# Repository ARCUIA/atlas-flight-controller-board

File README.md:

# atlas-flight-controller-v3
Repository to track KiCad (v9.0) Project for our spr26 competition flight controller.

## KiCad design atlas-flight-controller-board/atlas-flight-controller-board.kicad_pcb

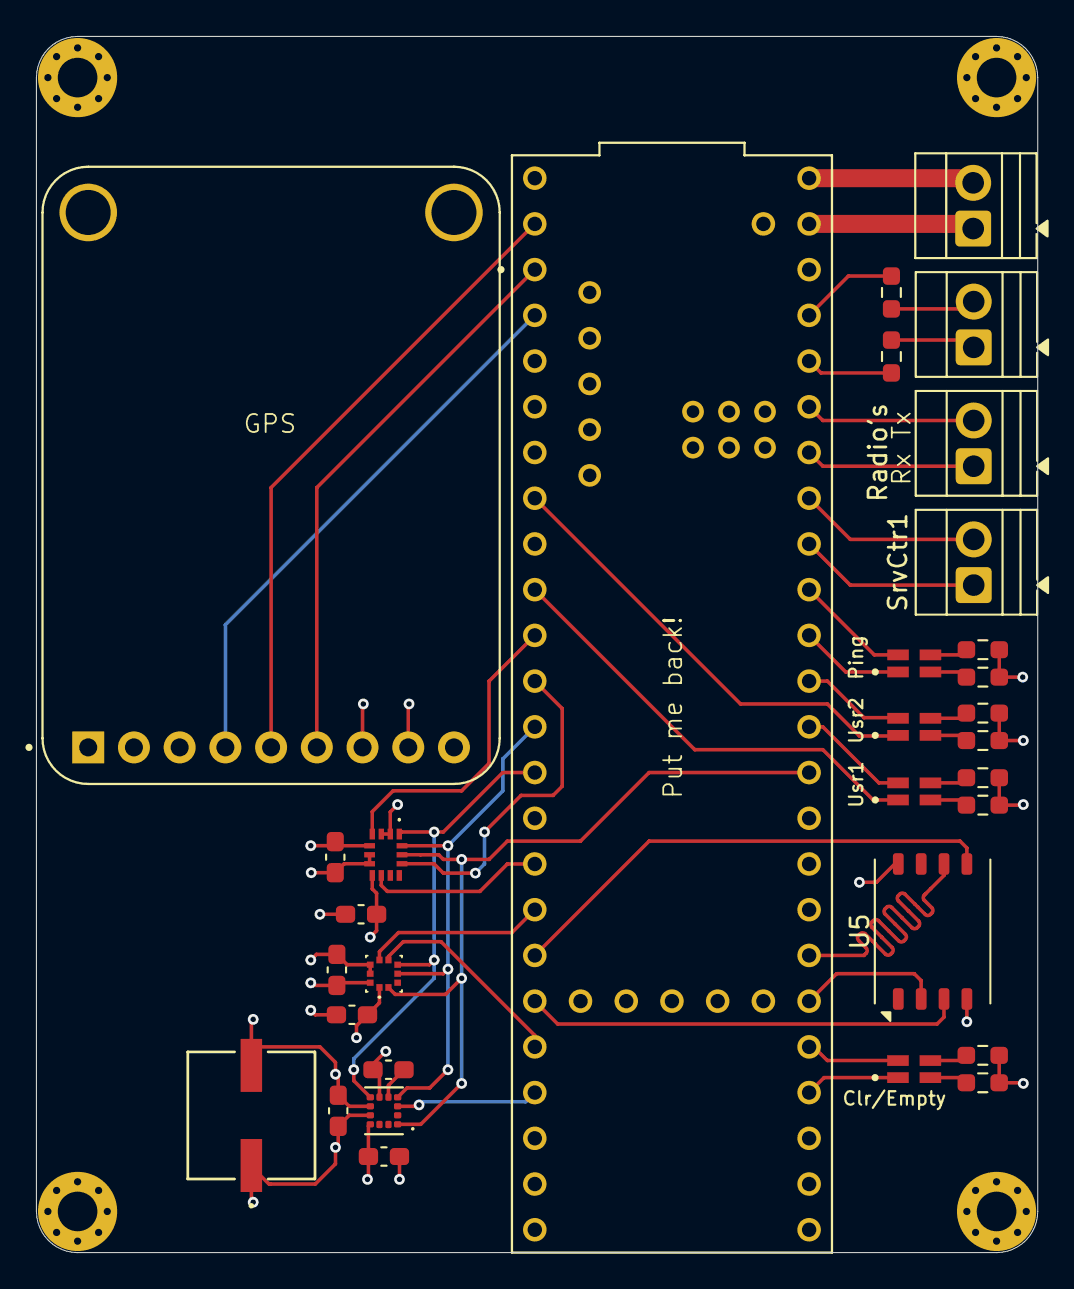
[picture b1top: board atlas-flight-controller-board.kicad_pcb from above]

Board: 4 copper layers, 55.6 x 67.6 mm, 32 parts (0 on the bottom side), 44 nets.

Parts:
C1, C2, C4, C5, C6, C8: 100 nF; C_0603_1608Metric_Pad1.08x0.95mm_HandSolder
C3: 10 uF; CAP_APA_0606_AVX
C7: 220 nF; C_0603_1608Metric_Pad1.08x0.95mm_HandSolder
D1, D2, D3, D4: APHBM2012LSURKZGKC; LED_APHBM2012LSURKZGKC
IC1: LSM6DSV80XTR; LSM6DSV16BXTR
IC2: LPS22HHTR
J1: LED Indicator Header; TerminalBlock_Xinya_XY308-2.54-2P_1x02_P2.54mm_Horizontal
J4: 5V Input Power; TerminalBlock_Xinya_XY308-2.54-2P_1x02_P2.54mm_Horizontal
R1, R2: 10; R_0603_1608Metric_Pad0.98x0.95mm_HandSolder
R3, R4, R5, R6, R7, R8, R9, R10: 100; R_0603_1608Metric_Pad0.98x0.95mm_HandSolder
Radio's: TerminalBlock_Xinya_XY308-2.54-2P_1x02_P2.54mm_Horizontal
SrvCtr1: Servo Ctrl; TerminalBlock_Xinya_XY308-2.54-2P_1x02_P2.54mm_Horizontal
U1: LIS2MDL; PQFN50P200X200X70-12N
U2: DEV-16771; MODULE_DEV-16771
U3: 746; XCVR_746
U5: LGA-8_8x6.2mm_P1.27mm

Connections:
+3V3: C1.2, C2.1, C3.1, C4.2, C5.2, C6.2, C8.1, IC1.5 (VDDIO), IC1.8 (VDD), IC2.1 (VDD_IO), IC2.10 (VDD), U1.9 (VDD), U1.10 (VDD_IO), U2.3.3V_1 (3.3V), U2.3.3V_2 (3.3V), U2.3.3V_3 (3.3V), U3.8 (VIN), U5.8 (VDD)
+5V: J4.2, U2.VIN
BARO_INT: IC2.7 (INT_DRDY), U2.25 (A11)
CS_BARO: IC2.6 (CS), U2.28 (RX7)
CS_IMU: IC1.12 (CS), U2.10 (CS1)
CS_MAG: U1.3 (CS), U2.29 (TX7)
CS_SD: U2.38 (A14), U5.2 (CS)
GND: C1.1, C2.2, C3.2, C4.1, C5.1, C6.1, C7.1, C8.2, IC1.2 (SDX), IC1.3 (SCX), IC1.6 (GND_1), IC1.7 (GND_2), IC2.3 (RESERVED), IC2.8 (GND_1), IC2.9 (GND_2), J4.1, R3.2, R4.2, R5.2, R6.2, R7.2, R8.2, R9.2, R10.2, U1.6 (GND), U1.8 (GND), U2.GND1 (GND), U2.GND2 (GND), U2.GND3 (GND), U2.GND4 (GND), U2.GND5 (GND), U2.USB_GND1 (USB_GND), U2.USB_GND2 (USB_GND), U3.7 (GND), U3.SH1 (SHIELD), U3.SH2 (SHIELD), U5.4 (GND)
GPS_FIX: U2.2 (OUT2), U3.4 (FIX)
IMU_INT1: IC1.4 (INT1), U2.9 (OUT1C)
IMU_INT2: IC1.9 (INT2), U2.24 (A10)
L_led: R1.1, U2.22 (A8)
MISO_MEMS: IC1.1 (SDO/SA0), IC2.5 (SDO/SA0), U1.7 (INT/DRDY/SDO), U2.12 (MISO)
MISO_SD: U2.39 (A15), U5.6 (MISO)
MOSI_MEMS: IC1.14 (SDA), IC2.4 (SDA/SDI/SDI/SDO), U1.4 (SDA/SDI/SDO), U2.11 (MOSI)
MOSI_SD: U2.26 (A12), U5.5 (MOSI)
unnamed: D1.2, R4.1
unnamed: D1.3, R3.1
unnamed: D2.2, R6.1
unnamed: D2.3, R5.1
unnamed: D3.2, R8.1
unnamed: D3.3, R7.1
unnamed: D4.2, R10.1
unnamed: D4.3, R9.1
unnamed: J1.1, R1.2
unnamed: J1.2, R2.1
unnamed: C7.2, U1.5 (C1)
Ping_Green: D1.4, U2.17 (A3)
Ping_Red: D1.1, U2.16 (A2)
R_led: R2.2, U2.23 (A9)
SCK_MEMS: IC1.13 (SCL), IC2.2 (SCL/SPC), U1.1 (SCL/SPC), U2.13 (SCK)
SCK_SD: U2.27 (A13), U5.3 (CLK)
SD_LED_Green: D4.4, U2.37 (CS3)
SD_LED_Red: D4.1, U2.36 (CS2)
Servo_1: SrvCtr1.1, U2.18 (A4)
Servo_2: SrvCtr1.2, U2.19 (A5)
UART_GPS_TX_MCU_RX: U2.0 (RX1), U3.5 (TX)
UART_MCU_TX_GPS_RX: U2.1 (TX1), U3.6 (RX)
UART_MCU_TX_RFD900_RX: Radio's.1 (Rx), U2.20 (A6)
UART_RFD900_TX_MCU_RX: Radio's.2 (Tx), U2.21 (A7)
USER_1_Green: D2.4, U2.14 (A0)
USER_1_Red: D2.1, U2.8 (TX2)
USER_2_Green: D3.4, U2.15 (A1)
USER_2_Red: D3.1, U2.6 (OUT1D)

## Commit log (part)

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2025-11-29 testing ssh write access
2025-11-29 testing vcs within kicad.
2025-11-30 Added Hierarchical Sheets. Finished IMU Schematic.
2025-11-30 Slightly changed default LPS22HH footprint. Finished LPS22HH schematic.
2025-12-01 Finished Mag Schematic. Modified Alum Poly Cap symbol + footprint.
2025-12-01 Fixed Footprints. Moving onto GPS Next
2026-01-30 wip commit, adding tennsy 4.1 and sd card.
2026-02-01 finishing up schematic for v1.
2026-02-01 wip commit
2026-02-09 Added Regulator, Leaving disconnected, and off pcb for now as teensy board does this automatically. Leaving on for future revs without teensy board
2026-03-01 Updating IMU to SPI
2026-03-01 Converted BARO to SPI
2026-03-01 Converting MAG to SPI. Have to remove Mag_Int to replace with SDO/MISO pin.
2026-03-03 wip with saves
2026-03-16 removing some olds symbols, adding some new things such as nand flash chip.
2026-03-17 Bare Schematic (No LEDS, etc added) finished. Begin PCB Layout.
2026-03-18 Re-arranging components, trying out different SPI routings
2026-03-18 Should have SPI routed in demo, need to implement.
2026-03-19 Sensor and Flash layout finished besides MISO, MOSI resistors (reduce ringing). Added plated M2 mounting holes.
2026-03-19 Fixing a couple things here and there. Need to add LEDs still and route external LEDs
2026-03-20 Done.
2026-03-20 generating and adding 3d model of the board
2026-03-23 Fab files via external tooling
2026-03-25 misc manufacturing files
2026-04-14 Test
2026-05-04 testing commit on new branch made by kicad. branch name: version2
